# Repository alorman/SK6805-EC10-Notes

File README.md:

# SK6805-EC10-Notes

Notes on the __smallest__ availible addressable LED to date!

**Author's note:** While you will definitely need a loupe or microscope to even see what you're doing, these can be a bit easier to solder than the 3535 and other large sizes. If you choose a low-temp solder and gently use hot air, you can get each LED to snap into place onto the solder pads. 

Above, you can see the EC10 modules next to a 3535 LED. These guys are SMOL.

## Purchasing
Adadfruit sells thes units as [Part Number 5849](https://www.adafruit.com/product/5849).
They can also be purchased on AliExpress in volume.  
Buy extras, you will lose some of these, since breathing on them the wrong way blows them away. 

## Datasheet 
[Datasheet from Adafruit](https://cdn-shop.adafruit.com/product-files/5849/SK6805-EC10-000_REV.01_EN.pdf)

## KiCad Files
I made footprint and symbol files availible for the EC10s.  
They can be found in `\SK6805-EC10-kicad-libraries`  
There is no 3d model included, because it didn't add much and made it much harder to see if the mask was right.  

## Test Fixture
Since I couldn't find a pre-made strip of the EC10 modules, I decided to make one. This can be easily fabbed from your favorite fab house. 
Full KiCad 8 files can be found in `\EC10-Test-PCB` 

## Power Profiling
I soldered 48 of the modules to my test fixture (2 got blown away by the hot air gun).
**Note** use low-temp solder and gentle hot air. I was able to swim the modules into place on flux without breaking any of the lenses. At least on the 1515, if you get them too hot, the lens/case breaks. 

### Setup
I connected my 48x strip to a Siglent SPD-3303X PSU that quotes current reading of +- 0.3% + 10ma, while there may be tiny test errors, this should provide a good bassis for power calculations. 

I used 5V as a supply voltage.

### Methodology
I cycled Red, Green then Blue through 0-255 individually, while recording the power usage. Then I ran all three together to make white from 0-255. 

The code can be found in `\test-code` and is designed for a Teensy, but would work on any Arduino. 

We can see a linear and similar progression for R, G and B. Correspondingly, we see that consumption roughly tripling for white, which makes sense.

The idle current can also be charachterized from the first few data points.

## Power Formula

### I<sub>consumed</sub>=((R+B+G)*0.013838)+0.4791

Where:  
`Iconsumed` = Current consumed **per LED** in mA  
`(R+B+G)` = Values for R, G and B in 0-255  
`0.4791` = Idle current draw in mA per module  

## Compared To 1515 Size
These are a good amount smaller than the pettite 1515 size. I documented the features of those [on this repo](https://github.com/alorman/sk6805-1515-info).

Here are the two compared:

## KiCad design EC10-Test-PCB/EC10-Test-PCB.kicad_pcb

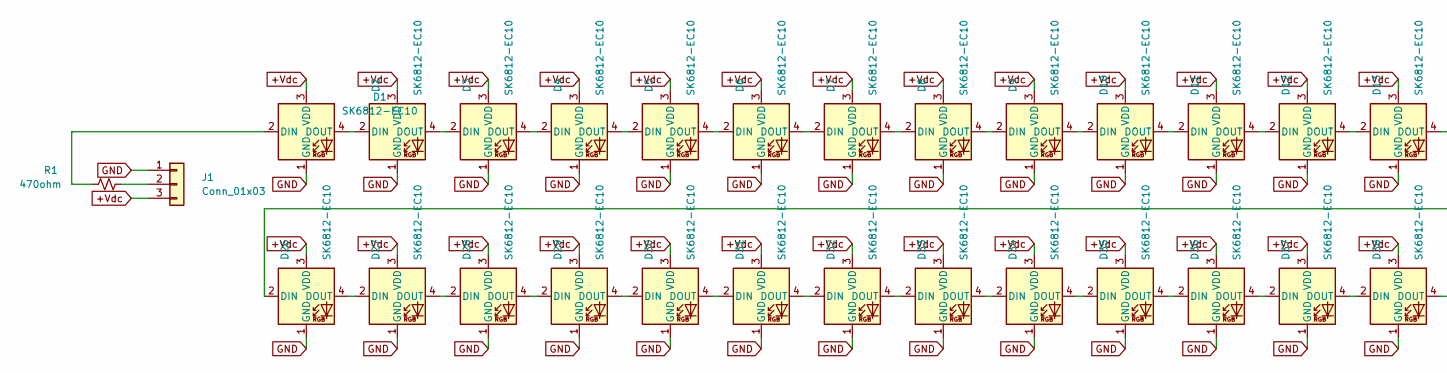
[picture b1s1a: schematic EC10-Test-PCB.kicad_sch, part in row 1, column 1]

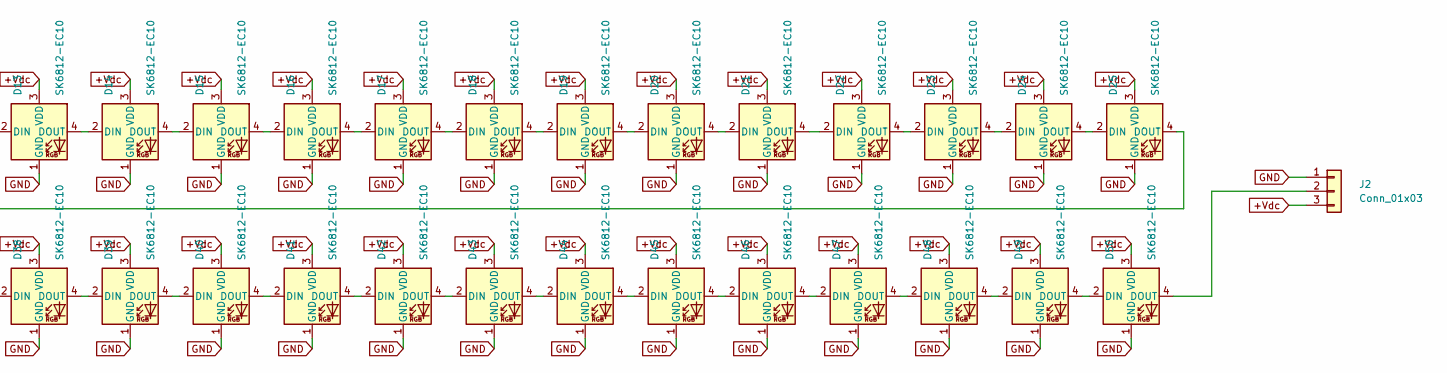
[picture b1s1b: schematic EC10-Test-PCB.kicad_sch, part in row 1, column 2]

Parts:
D1, D2, D3, D4, D5, D6, D7, D8, D9, D10, D11, D12, D13, D14, D15, D16, D17, D18, D19, D20, D21, D22, D23, D24, D25, D26, D27, D28, D29, D30, D31, D32, D33, D34, D35, D36, D37, D38, D39, D40, D41, D42, D43, D44, D45, D46, D47, D48, D49, D50: SK6812-EC10; SK6805-EC10
J1, J2: Conn_01x03; PinHeader_1x03_P2.54mm_Vertical
R1: 470ohm; R_0603_1608Metric

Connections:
+Vdc: D1.3 (VDD), D2.3 (VDD), D3.3 (VDD), D4.3 (VDD), D5.3 (VDD), D6.3 (VDD), D7.3 (VDD), D8.3 (VDD), D9.3 (VDD), D10.3 (VDD), D11.3 (VDD), D12.3 (VDD), D13.3 (VDD), D14.3 (VDD), D15.3 (VDD), D16.3 (VDD), D17.3 (VDD), D18.3 (VDD), D19.3 (VDD), D20.3 (VDD), D21.3 (VDD), D22.3 (VDD), D23.3 (VDD), D24.3 (VDD), D25.3 (VDD), D26.3 (VDD), D27.3 (VDD), D28.3 (VDD), D29.3 (VDD), D30.3 (VDD), D31.3 (VDD), D32.3 (VDD), D33.3 (VDD), D34.3 (VDD), D35.3 (VDD), D36.3 (VDD), D37.3 (VDD), D38.3 (VDD), D39.3 (VDD), D40.3 (VDD), D41.3 (VDD), D42.3 (VDD), D43.3 (VDD), D44.3 (VDD), D45.3 (VDD), D46.3 (VDD), D47.3 (VDD), D48.3 (VDD), D49.3 (VDD), D50.3 (VDD), J1.3, J2.3
GND: D1.1 (GND), D2.1 (GND), D3.1 (GND), D4.1 (GND), D5.1 (GND), D6.1 (GND), D7.1 (GND), D8.1 (GND), D9.1 (GND), D10.1 (GND), D11.1 (GND), D12.1 (GND), D13.1 (GND), D14.1 (GND), D15.1 (GND), D16.1 (GND), D17.1 (GND), D18.1 (GND), D19.1 (GND), D20.1 (GND), D21.1 (GND), D22.1 (GND), D23.1 (GND), D24.1 (GND), D25.1 (GND), D26.1 (GND), D27.1 (GND), D28.1 (GND), D29.1 (GND), D30.1 (GND), D31.1 (GND), D32.1 (GND), D33.1 (GND), D34.1 (GND), D35.1 (GND), D36.1 (GND), D37.1 (GND), D38.1 (GND), D39.1 (GND), D40.1 (GND), D41.1 (GND), D42.1 (GND), D43.1 (GND), D44.1 (GND), D45.1 (GND), D46.1 (GND), D47.1 (GND), D48.1 (GND), D49.1 (GND), D50.1 (GND), J1.1, J2.1
unnamed: D1.2 (DIN), R1.1
unnamed: D1.4 (DOUT), D2.2 (DIN)
unnamed: D2.4 (DOUT), D3.2 (DIN)
unnamed: D3.4 (DOUT), D4.2 (DIN)
unnamed: D4.4 (DOUT), D5.2 (DIN)
unnamed: D5.4 (DOUT), D6.2 (DIN)
unnamed: D6.4 (DOUT), D7.2 (DIN)
unnamed: D7.4 (DOUT), D8.2 (DIN)
unnamed: D8.4 (DOUT), D9.2 (DIN)
unnamed: D9.4 (DOUT), D10.2 (DIN)
unnamed: D10.4 (DOUT), D11.2 (DIN)
unnamed: D11.4 (DOUT), D12.2 (DIN)
unnamed: D12.4 (DOUT), D13.2 (DIN)
unnamed: D13.4 (DOUT), D14.2 (DIN)
unnamed: D14.4 (DOUT), D15.2 (DIN)
unnamed: D15.4 (DOUT), D16.2 (DIN)
unnamed: D16.4 (DOUT), D17.2 (DIN)
unnamed: D17.4 (DOUT), D18.2 (DIN)
unnamed: D18.4 (DOUT), D19.2 (DIN)
unnamed: D19.4 (DOUT), D20.2 (DIN)
unnamed: D20.4 (DOUT), D21.2 (DIN)
unnamed: D21.4 (DOUT), D22.2 (DIN)
unnamed: D22.4 (DOUT), D23.2 (DIN)
unnamed: D23.4 (DOUT), D24.2 (DIN)
unnamed: D24.4 (DOUT), D25.2 (DIN)
unnamed: D25.4 (DOUT), D26.2 (DIN)
unnamed: D26.4 (DOUT), D27.2 (DIN)
unnamed: D27.4 (DOUT), D28.2 (DIN)
unnamed: D28.4 (DOUT), D29.2 (DIN)
unnamed: D29.4 (DOUT), D30.2 (DIN)
unnamed: D30.4 (DOUT), D31.2 (DIN)
unnamed: D31.4 (DOUT), D32.2 (DIN)
unnamed: D32.4 (DOUT), D33.2 (DIN)
unnamed: D33.4 (DOUT), D34.2 (DIN)
unnamed: D34.4 (DOUT), D35.2 (DIN)
unnamed: D35.4 (DOUT), D36.2 (DIN)
unnamed: D36.4 (DOUT), D37.2 (DIN)
unnamed: D37.4 (DOUT), D38.2 (DIN)
unnamed: D38.4 (DOUT), D39.2 (DIN)
unnamed: D39.4 (DOUT), D40.2 (DIN)
unnamed: D40.4 (DOUT), D41.2 (DIN)
unnamed: D41.4 (DOUT), D42.2 (DIN)
unnamed: D42.4 (DOUT), D43.2 (DIN)
unnamed: D43.4 (DOUT), D44.2 (DIN)
unnamed: D44.4 (DOUT), D45.2 (DIN)
unnamed: D45.4 (DOUT), D46.2 (DIN)
unnamed: D46.4 (DOUT), D47.2 (DIN)
unnamed: D47.4 (DOUT), D48.2 (DIN)
unnamed: D48.4 (DOUT), D49.2 (DIN)
unnamed: D49.4 (DOUT), D50.2 (DIN)
unnamed: D50.4 (DOUT), J2.2
unnamed: J1.2, R1.2

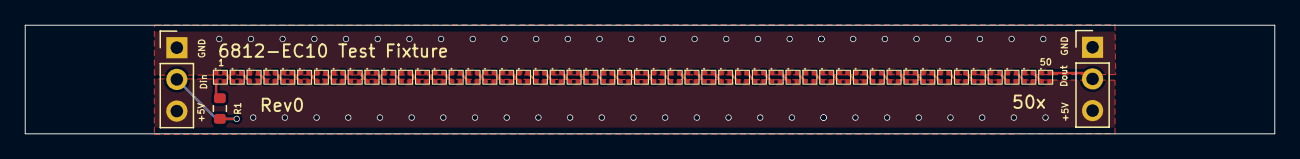
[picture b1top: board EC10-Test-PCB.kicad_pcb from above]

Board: 2 copper layers, 100.1 x 8.7 mm, 53 parts (0 on the bottom side), 54 nets.

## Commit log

2025-02-17 test pcb release to fab
2025-03-05 add notes, pcb files, results and photos
2025-03-05 docs updates
2025-03-05 docs update
